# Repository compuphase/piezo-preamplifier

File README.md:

# Piezo Pickup Preamplifier
These are simple designs for high impedance preamplifiers. They are intended for
piezo pickups, and in particular for piezo bridge pickups for (nylon-stringed)
guitars. There is a single-channel and a dual-channel design.

The designs are in KiCad. PDFs with the schematics, and the Gerber files for the
PCBs are also provided.

## Single channel
This circuit was built for use with a Shadow SH097 bridge pickup. The pickup has
a capacitance of 680pF. Yet, input impedance of this preamplifier is *only*
1M&Omega;, because the basses were already quite pronounced.

It is a pretty classic opamp circuit. Amplification is fixed at 1&times;
&mdash;the circuit is only to adapt the impedance (piezo bridge pickups are
pretty loud already). The main feature of the circuit is that it is compact,
and especially narrow. The idea is to fit this preamplifier into a slot
immediately below the pickup.

The PDF with the schematic also shows the wiring for a TRS socket and battery;
these are not on the PCB, and technically not part of the circuit). The main
idea of the wiring is that the battery is connected only when the jack plug is
inserted. When the plug is pulled out of the instrument, the battery is disconnected.

## Dual channel
This circuit was built for the ARTEC PG-333 bridge pickup. The pickup connects two
piezo bridge pickups in parallel, where each pickup covers only three strings. For
use with this preamplifier, the two piezo segments have to be separated, and each
connected to a separate input of the preamplifer. Input impedance for each channel
is roughly 2M&Omega;.

I measured one of the piezo segments to have a capacitance of 580pF and the other
as 970pF &mdash;to my surprise. This being the case, you will want to position
the 580pF segment at the treble side, and the 970pF segment at the bass side of
the bridge.

The dual-channel circuit has two independent impedance converters, and a third
preamplifier to mix the outputs of the first stages. The balance of the "treble"
side relative to the "bass" side, can be adjusted with a trimmer pot.

The preamplifier has a "bass boost" filter that boosts the frequencies below
roughly 250 Hz by roughly 5 dB. The resonance chamber of a classical guitar has
a main resonant frequency at around 200 to 250 Hz, which is what the bass boost
emulates.

---

Copyright 2023-2025, CompuPhase, Thiadmer Riemersma<br>
This work is licensed under a Creative Commons Attribution-NonCommercial-ShareAlike 4.0 International License (https://creativecommons.org/licenses/by-nc-sa/4.0/).

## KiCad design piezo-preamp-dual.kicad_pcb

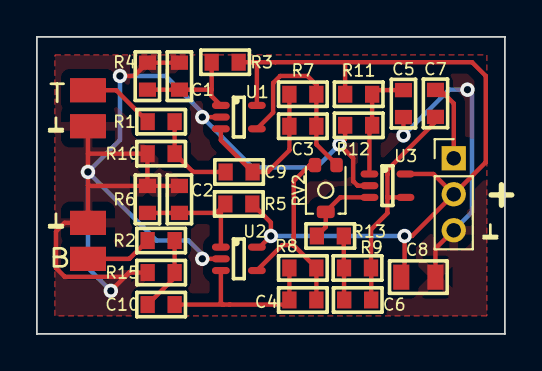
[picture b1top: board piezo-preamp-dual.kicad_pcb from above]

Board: 2 copper layers, 26.0 x 16.5 mm, 31 parts (0 on the bottom side), 17 nets.

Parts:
C1, C2, C5: 220n; 0603
C3, C4: 68p; 0603
C6: 22n; 0603
C7: 1u; 0603
C8: 4u7; 0805
C9, C10: 100k; 0603
J3, J4: piezo; PinHeader_1x02_P2.00mm_Vertical
J5: output; PinHeader_1x03_P2.00mm_Vertical
R1, R2: 2M2; 0603
R3, R4, R5, R6, R10, R11, R12, R15: 100k; 0603
R7, R8: 470k; 0603
R9, R13: 22k; 0603
RV2: 20k; TC42
U1, U2, U3: OPA323; SOT353

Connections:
+5V: C8.1, J5.2, R3.1, R5.1, R11.1, U1.5 (V+), U2.5 (V+), U3.5 (V+)
GND: C1.2, C2.2, C5.2, C8.2, J3.2, J4.2, J5.3, R4.2, R6.2, R10.2, R12.2, R15.2, U1.2 (V-), U2.2 (V-), U3.2 (V-)
unnamed: C3.2, R7.2, RV2.1, U1.4
unnamed: C4.2, R8.2, RV2.3, U2.4
unnamed: C6.1, R9.1, R13.2
unnamed: C6.2, C7.1, R9.2, U3.4
unnamed: J3.1, R1.1
unnamed: J4.1, R2.1
unnamed: C7.2, J5.1
unnamed: C9.1, R1.2, R10.1
unnamed: C10.1, R2.2, R15.1
unnamed: C1.1, R3.2, R4.1, U1.1 (+)
unnamed: C3.1, C9.2, R7.1, U1.3 (-)
unnamed: C2.1, R5.2, R6.1, U2.1 (+)
unnamed: C4.1, C10.2, R8.1, U2.3 (-)
unnamed: C5.1, R11.2, R12.1, U3.1 (+)
unnamed: R13.1, RV2.2, U3.3 (-)

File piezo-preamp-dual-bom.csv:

Reference,Value,Footprint,Qty,ProductNumber
"C1,C2,C5",220n,VisualPlace:0603,3,
"C3,C4",68p,VisualPlace:0603,2,
C6,22n,VisualPlace:0603,1,
"C7,C9,C10",1u,VisualPlace:0603,3,
C8,4u7,VisualPlace:0805,1,
"R1,R2",2M2,VisualPlace:0603,2,
"R3,R4,R5,R6,R10,R11,R12,R15",100k,VisualPlace:0603,8,
"R7,R8",470k,VisualPlace:0603,2,
"R9,R13",22k,VisualPlace:0603,2,
RV2,20k,TrimPots:TC42,1,3312J-1-203E
"U1,U2,U3",OPA323,VisualPlace:SOT353,3,OPA323IDCKR

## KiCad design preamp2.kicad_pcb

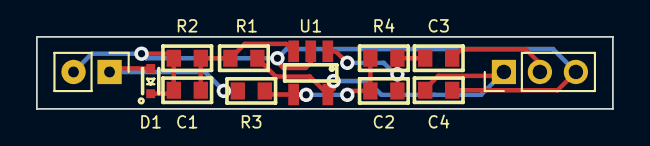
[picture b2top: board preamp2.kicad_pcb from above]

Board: 2 copper layers, 32.0 x 4.0 mm, 12 parts (0 on the bottom side), 7 nets.

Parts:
C1, C3, C4: 1u; 0603
C2: 10p; 0603
D1: TVS 6V; SOD523
J1: piezo; PinHeader_1x02_P2.00mm_Vertical
J2: output; PinHeader_1x03_P2.00mm_Vertical
R1, R2: 22k; 0603
R3, R4: 820k; 0603
U1: OPA1677; SOT23-5

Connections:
+9V: C4.1, J2.1, R1.1, U1.5 (V+)
GND: C1.2, C4.2, D1.1 (A1), J1.2, J2.3, R2.2, U1.2 (V-)
unnamed: C2.2, C3.1, R4.2, U1.1
unnamed: D1.2 (A2), J1.1, R3.1
unnamed: C3.2, J2.2
unnamed: C1.1, R1.2, R2.1, U1.3 (+)
unnamed: C2.1, R3.2, R4.1, U1.4 (-)

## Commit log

2023-12-25 Add PDF of schematic.
2023-12-27 Tweaked some component values.
2023-12-27 Update README.md
    A few more details.
2023-12-27 Tweaked some component values, again.
2023-12-27 Update README.md
    Added info on input impedance.
2023-12-27 Update README.md
    Correction in the description for the input impedance and frequency cut-off point.
2024-01-05 A few more tweaks in components, after more measurements.
2024-01-19 Rename design files for single-channel amplifier.
2024-01-19 Rename Gerber files for single-channel piezo amplifier.
2024-01-19 Add dual-channel piezo preamplifier.
2024-01-19 Update readme to include a description of the dual-channel preamplifier.
2024-01-31 The TVS diodes were removed from the "dual-channel" design. The PCB is slighly smaller as a result.
    The parasitic capacitance of the TVS diodes had a negative effect on the sound. In addition, they were redundant; the inputs of the OPA1677 are already protected against overvoltage, so the 1 MOhm re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
2024-07-14 Added bass-boost filter (dual-channel preamp only). Added Bill-Of-Materials file. Fixed PDF of the schematic (turned out to be unreadable).
2025-04-01 Reduce (peak) voltage of the piezo pick-ups, to avoid saturatating the opamps. Switch opamps to OPA323, to avoid clamping diodes on input. Higher input impedance.
2025-04-01 Update description of the dual-channel preamp.
